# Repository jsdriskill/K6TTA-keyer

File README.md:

# K6TTA Keyer (Raspberry Pi Pico)

CW paddle keyer for RP2040 with SSD1306 UI, rotary encoder setup, flash-backed settings, and a USB composite device: K1EL WinKeyer v2-style serial port, a USB audio source that mirrors the sidetone, and USB MIDI key events.

## Pins

| Function | GPIO |
| --- | --- |
| Dit paddle (active low, external pull-up) | 2 |
| Dash paddle (active low, external pull-up) | 3 |
| TX key out | 4 |
| Sidetone (PWM sine) | 5 |
| Encoder A | 6 |
| Encoder B | 7 |
| Encoder switch | 8 |
| Message button 1 / 2 / 3 (active low, pull-up) | 9 / 10 / 11 |
| OLED SDA (I2C0) | 12 |
| OLED SCL | 13 |
| SSD1306 address | 0x3C |

**Sidetone (pin 5).** A sine wave made with the PWM as a one-pin DAC: 11-bit steps, about 61 kHz carrier and sample rate, a 256-point sine table with linear interpolation, and 4 ms attack/release ramps (no key clicks). The pin swings between 0 V and 3.3 V, so use a series resistor and, for a speaker, a coupling capacitor; a piezo can be driven directly. A small low-pass (for example 1 kohm + 100 nF) removes the 61 kHz carrier if you feed an amplifier. The tone is always at full amplitude, so scale it down with the series resistor or an external volume control. The wave comes from a PWM wrap interrupt on core 0, about 3 % of that core; the pin is parked low whenever the tone is off.

## Build

Uses Pico SDK 2.3.1 from `~/.pico-sdk` when the VS Code Pico extension CMake snippet is present.

```bash
export PICO_SDK_PATH="$HOME/.pico-sdk/sdk/2.3.1"
cmake -S . -B build -DPICO_BOARD=pico
cmake --build build
```

For Pico 2, pass `-DPICO_BOARD=pico2`.

Flash `build/k6tta-keyer.uf2` by holding BOOTSEL, plugging USB, and copying the UF2.

## USB

The keyer enumerates as one composite device ("K6TTA Keyer"):

| Function | What the host sees |
| --- | --- |
| Serial (CDC) | WinKeyer v2-style port |
| Audio | A mono 48 kHz, 16-bit USB microphone ("K6TTA Keyer Sidetone", UAC2). It carries the same sidetone as the buzzer: same frequency, silent when sidetone is disabled in the menu, 4 ms attack/release ramps. Windows needs 10 (1703) or later; macOS and Linux work out of the box. |
| MIDI | A class-compliant MIDI device ("K6TTA Keyer MIDI") |

### MIDI messages

MIDI follows the [Vail adapter MIDI spec](https://github.com/Vail-CW/vail-adapter/blob/master/docs/MIDI_INTEGRATION_SPEC.md), which web CW tools such as Vail and VBand-style adapters use. Channel 1:

| Event | Message |
| --- | --- |
| Key down (each dit/dah element, or straight key down) | Note On, note 0, velocity 127 (`90 00 7F`) |
| Key up | Note Off, note 0 (`80 00 00`) |

The keyer does its own iambic/ultimatic/bug timing, so it reports keyed elements on note 0 (as Vail adapters do in their keyer modes) rather than raw paddle contacts on notes 1 and 2. Incoming MIDI (mode, speed, keyer-type messages) is ignored: configure the keyer from its menu or over WinKeyer.

### Keyer behaviour (K3NG-compatible)

Paddle element generation follows the [K3NG keyer](https://github.com/k3ng/k3ng_cw_keyer): one memory per paddle; while an element and its gap are timed only the *opposite* paddle is sampled, and both paddles are sampled by level when they end. The next element is the remembered opposite one, else a repeat. Iambic A drops the memory when a squeeze is gone by the end of the element. Ultimatic mode uses K3NG's last-touch closure logic. Weighting changes key-down time without changing the spacing (dit + gap = 2 units, dah + gap = 4 units at a 3:1 ratio, as in K3NG), and autospace adds 2 units so the character gap is 3. Differences: paddle contacts are debounced (2 ms), and bug mode only keys down for a dah that is still held. The behaviour is checked against a literal port of K3NG's logic on random paddle input (all four modes) and against its timing formulas.

## WinKeyer serial port

Open the CDC port (`/dev/ttyACM0`, any baud rate), send the host-open command (`00 02`; the reply is the revision byte, 23), then:

- **Text** (ASCII `0x20`-`0x7F`) is sent as Morse through the same timing as the paddles (speed, weighting, dash ratio, sidetone, key output, USB audio and MIDI). It goes through a 128 character buffer. Touching a paddle cancels whatever is queued (break-in).
- **Status byte** (`11` + `BUSY`/`BREAKIN`/`XOFF`) is sent whenever it changes, and on request (`15`). `XOFF` is set when the buffer is more than two thirds full; the `WAIT` and `KEYED` bits are never set.
- **Echo**: characters are echoed as they start sending when the mode register's serial-echo bit (bit 2) is set, and characters sent on the paddles are decoded and echoed when paddle echo (bit 6) is set.
- **Setup commands implemented**: sidetone (`01`, 4000/n Hz), speed (`02`), weighting (`03`), speed pot read (`07`, always minimum), clear buffer (`0A`), mode register (`0E`: keyer mode, paddle swap, autospace, echo bits), status request (`15`), and admin open/close/reset/echo test.
- **Accepted but ignored** (their parameter bytes are consumed so the stream stays in sync): PTT timing, speed pot setup, pause, pin config, key immediate, HSCW, Farnsworth, load defaults, first extension, key compensation, paddle switchpoint, software paddle, buffer pointer, dah ratio, PTT, and the buffered commands (key, wait, merge letters, speed change, HSCW, NOP).
- **Not implemented**: admin calibrate, paddle and speed A2D, get values and EEPROM commands produce no reply.

### Notes

- All USB runs on core 1, so the display and encoder cannot disturb the audio. Core 0 only passes the key state across.
- Saving settings pauses core 1 for a few tens of milliseconds, so the audio may click once when you leave the setup menu.
- The device uses the TinyUSB test vendor id (`0xCafe`). Replace `idVendor`/`idProduct` in `usb_descriptors.c` with your own allocation if you distribute it.
- USB stdio (`printf` over USB) is no longer available; the USB port belongs to the composite device.

## Controls

- Encoder: WPM on the home screen; current menu value in setup
- Click: enter setup, then advance items; last click saves to flash and returns home

## Power-up

The paddle inputs (GPIO 2 and 3) are plain inputs with the internal pull-up and pull-down both off, so each needs an external pull-up resistor to 3.3 V (never 5 V). I use a stiff 680 ohm pull-up, which passes about 5 mA through the key's contacts when they close. That wetting current keeps the contacts clean and reliable, and the low impedance also makes the lines harder for RF to disturb. A weaker pull-up such as 10 kohm also works. Without it the lines float and the keyer sees random paddle contacts. The resistor takes a moment to charge any capacitance on the lines (filter capacitors, a long cable). The keyer waits up to 50 ms at start-up for both lines to go high, and then ignores the paddles until it has seen both released, so contacts that are closed or still settling at power-up never send anything.

## Setup menu

Click the encoder to open the menu and again to step to the next page. Each page shows what is being changed on the top line (large type, centred), its value on the line below (large type, inverted), and the page number (for example 3/9) at the bottom. Turn the encoder to change the value.

## Main screen

The speed (large digits) and the mode are shown at boot. As soon as anything is sent, the screen switches to the text that has been sent, in large type: four lines of 11 characters, word wrapped, scrolling up one line at a time when the bottom line is full. It shows what the paddles sent (decoded with the same Morse table the WinKeyer sender uses; the prosigns BT, AR and SK are shown as `<BT>`, `<AR>` and `<SK>`, and a pattern that is not a character shows `*`), plus stored messages and text sent from the WinKeyer port. The text stays until reboot. Turning the encoder, or a speed change from the WinKeyer host, shows the speed for 3 seconds (each change restarts the timer), then the text returns. In bug and straight-key modes nothing is decoded and the speed screen stays. The TEXT setting in the setup menu (last page) turns the text display off, which leaves the speed screen on all the time.

## Stored messages

Three messages of up to 32 characters each, on the buttons at GPIO 9, 10 and 11 (to ground).

- Short press: send the message at the current speed. Press again while it is sending to abort. Touching a paddle also aborts. A slot with no message goes straight to edit mode.
- Hold 3 seconds: edit that slot. Button presses are ignored while the setup menu is open.
- Editing starts with the cursor just after the stored message (on "done"). The whole message is shown in large type, four lines of 11 characters, with the cursor inverted. The encoder chooses the character at the cursor (done, space, A-Z, 0-9, `. , ? /`), and the encoder button stores it and moves on. Button 1 / button 2 move the cursor back / forward without changing anything (an unstored change is dropped). Choosing "done" and clicking saves the message up to the cursor; "done" at the first position leaves the slot empty. Filling all 32 positions saves and exits automatically.
- The messages live in the settings flash page; saving takes about 50 ms, during which USB audio drops out.

## Hardware

KiCad projects for the main and front boards are in [`hardware/`](hardware/README.md) (draft v0.1: parts placed, not yet routed).

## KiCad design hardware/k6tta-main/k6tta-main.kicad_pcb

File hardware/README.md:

# K6TTA keyer hardware v0.1

Two KiCad 10 projects. Both boards are routed with GND pours on both layers and pass DRC
(only cosmetic silkscreen and library-version warnings remain).

* `k6tta-main/` main board, 64 x 56 mm: RP2040-Zero on sockets (USB-C to the rear), rig jack at the rear facing back,
  paddle jack front-right, headphone jack left with the thumbwheel in front of it, 2x8 right-angle socket on the front edge.
* `k6tta-front/` front board, 76 x 54 mm: 0.96in SSD1306 OLED (on a 1x4 socket), EC11 encoder, three 12 mm message buttons,
  2x8 straight header soldered on the BACK so it plugs into the main board's right-angle socket.

Pin assignments come from `config.h` (GP2 dit, GP3 dah, GP4 TX key, GP5 sidetone, GP6-8 encoder,
GP9-11 message buttons, GP12/13 I2C).

The KiCad files are the source of truth. The scripts in `generator/` produced the first unrouted draft and the
netlist/BOM CSVs; part positions in them no longer match the routed boards.

## Checked

* **RP2040-Zero pinout** (`K6TTA:RP2040-Zero_Socketed`): pad 1 = 5V top-left with USB-C up, GP0 top-right,
  GP9..GP13 on the short row opposite the USB (GP13 at the left). Confirmed against the clone in use.
* **Thumbwheel RV1** (Alps RK10J11E0034, `K6TTA:Alps_RK10J_Thumbwheel_5pin`): footprint checked against the Alps
  PC board drawing. It is a single pot: pads 1, 3, 5 = datasheet pins 1 (end), 2 (wiper), 3 (end); pads 2 and 4
  are dummy terminals. Wired as a rheostat: VOL_IN to pad 1, wiper (pad 3) tied to pad 5 and the headphones.

## Still to check

* **Board-to-board header**: main J5 odd pins (rear row of the right-angle socket, upper opening) carry the signals;
  front J1 even pins (upper row) mate with them. Check the height of the socket openings against where the front board sits.
* **OLED module**: pin order GND VCC SCL SDA; it is held only by its socket, so support it with standoffs or the panel.
* **LCSC numbers**: all JLCPCB-placed parts are chosen from the Basic library (the "JLC class" column says which were
  confirmed); re-check stock when you order.

R8 (speaker series resistor) is a 1/2 W axial part you solder, so you can change the speaker level.

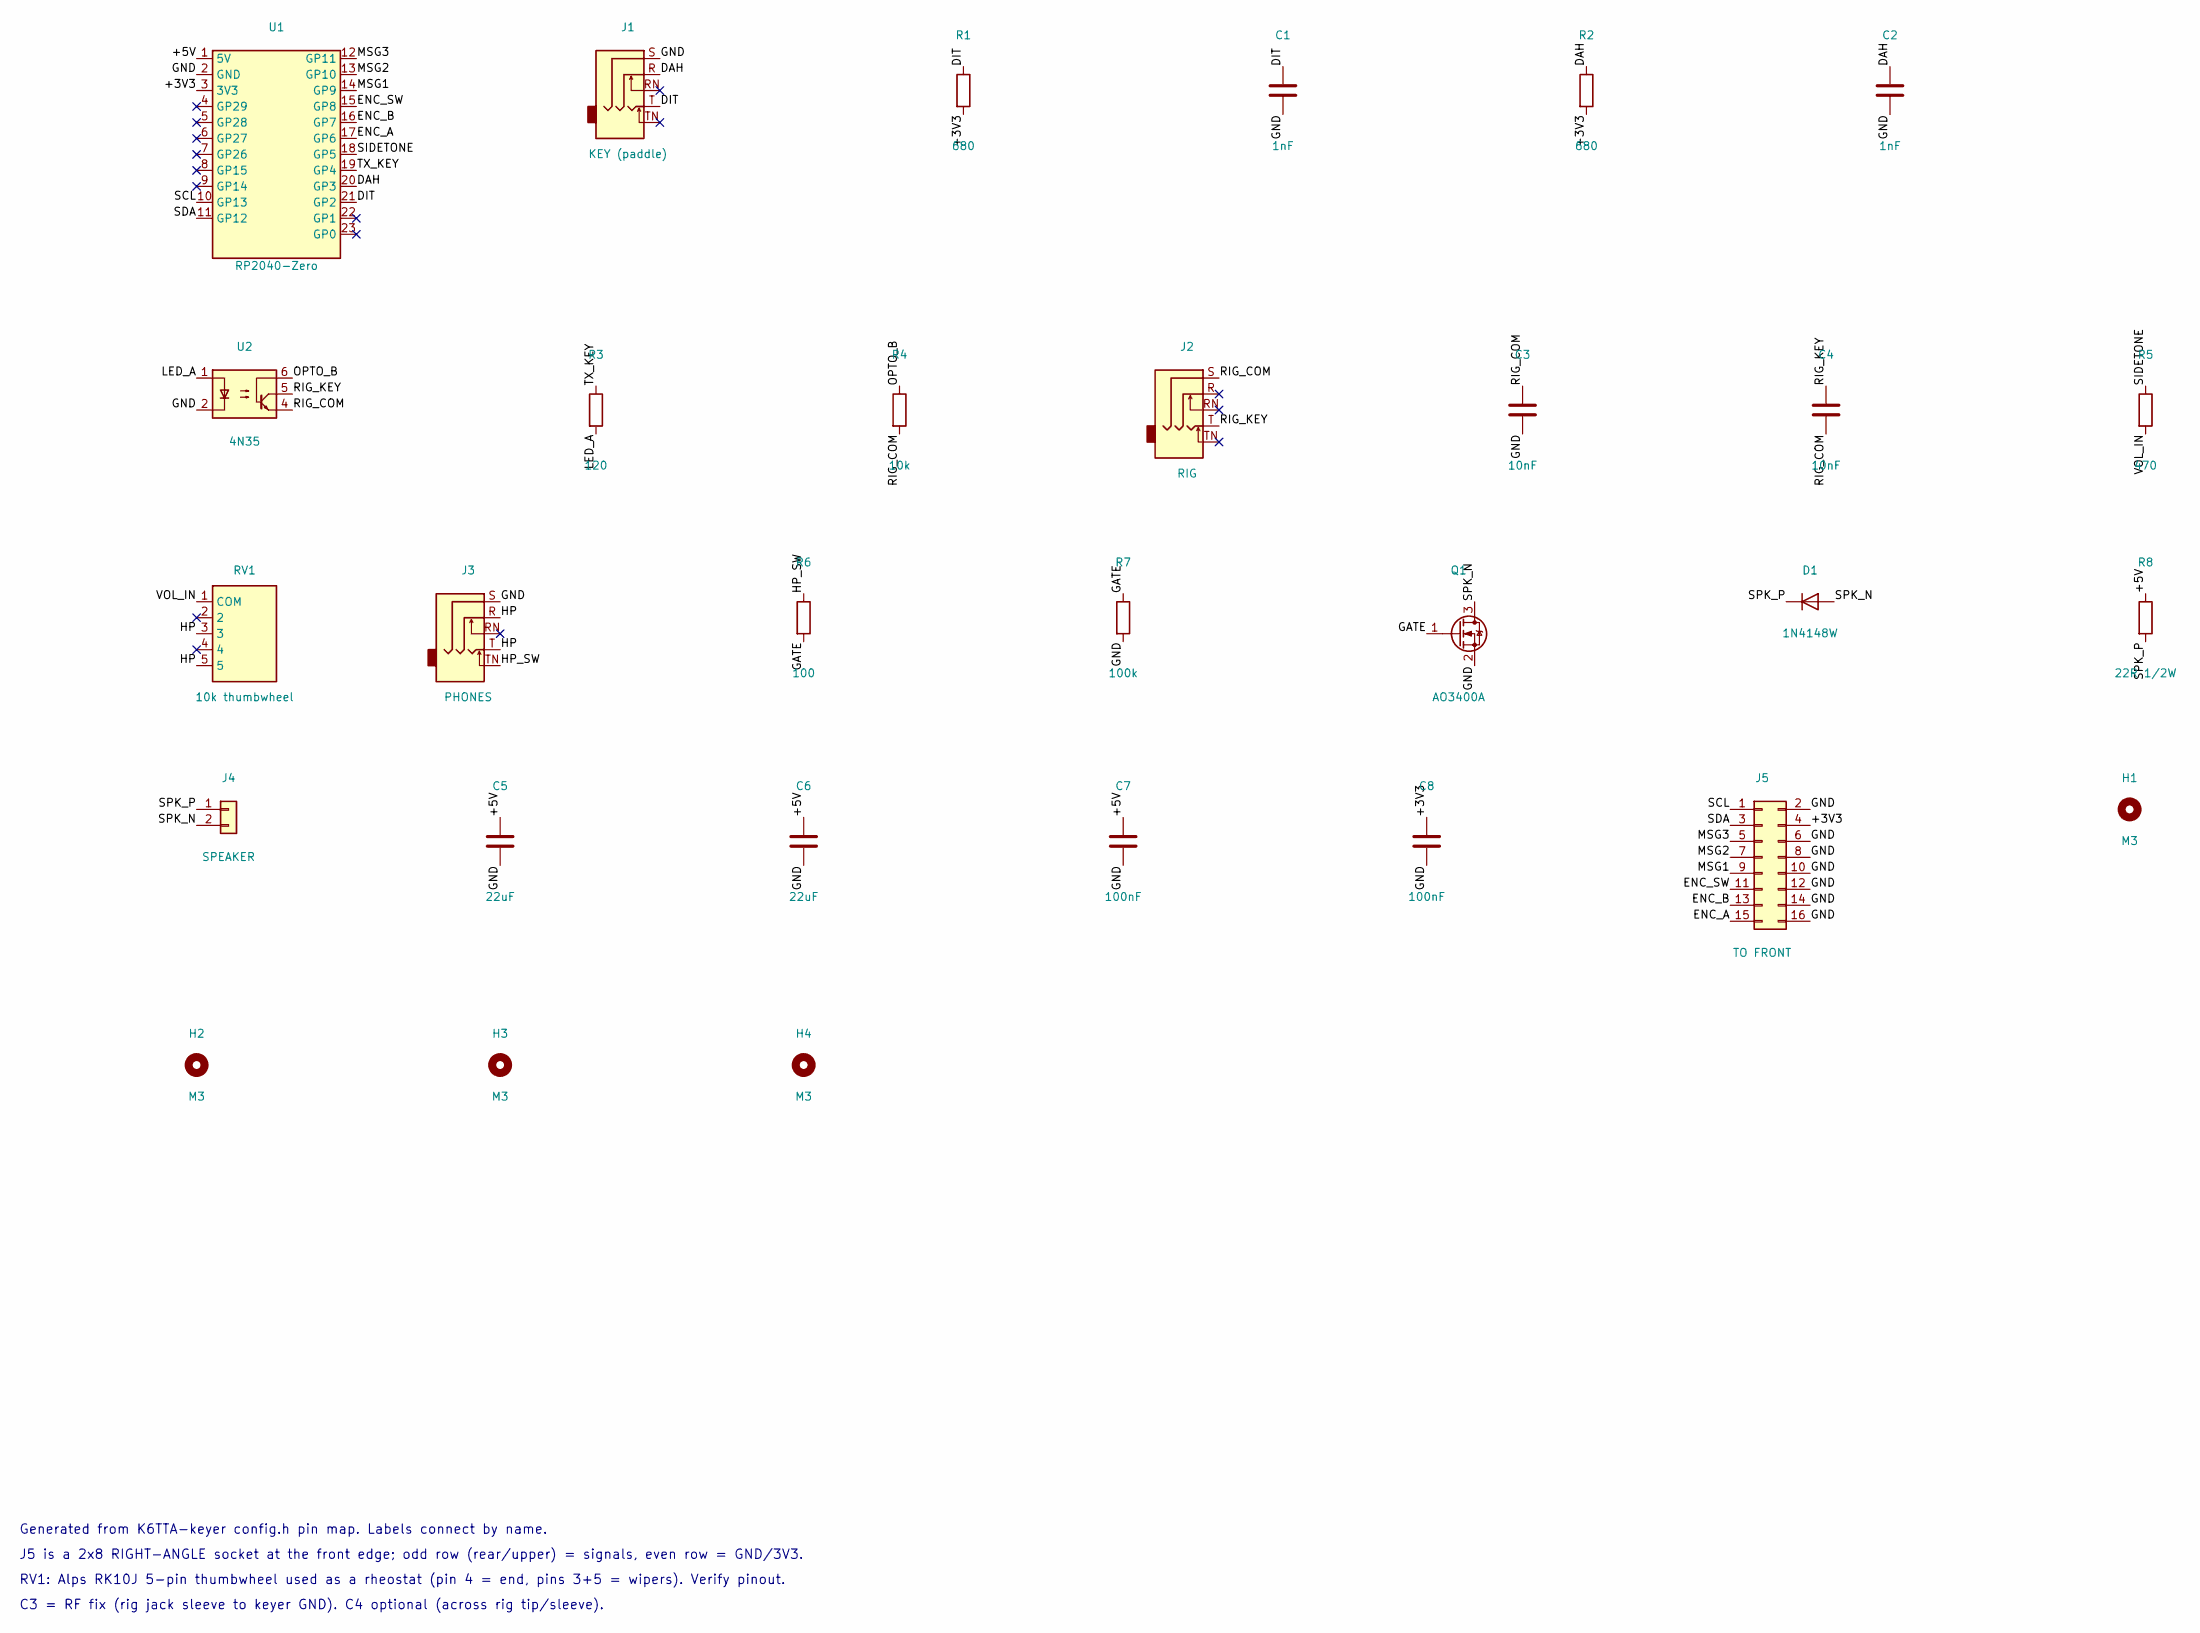
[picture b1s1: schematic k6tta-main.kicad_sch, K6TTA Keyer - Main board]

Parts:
C1, C2: 1nF; C_0805_2012Metric; LCSC C46653
C3, C4: 10nF; C_0805_2012Metric; LCSC C1710
C5, C6: 22uF; C_0805_2012Metric; LCSC C45783
C7, C8: 100nF; C_0805_2012Metric; LCSC C49678
D1: 1N4148W; D_SOD-123; LCSC C81598
H1, H2, H3, H4: M3; MountingHole_3.2mm_M3
J1: KEY (paddle); Jack_3.5mm_CUI_SJ1-3525N_Horizontal; MPN/Notes Same Sky SJ1-3525N
J2: RIG; Jack_3.5mm_CUI_SJ1-3525N_Horizontal; MPN/Notes Same Sky SJ1-3525N
J3: PHONES; Jack_3.5mm_CUI_SJ1-3525N_Horizontal; MPN/Notes Same Sky SJ1-3525N
J4: SPEAKER; JST_XH_B2B-XH-A_1x02_P2.50mm_Vertical; MPN/Notes JST B2B-XH-A
J5: TO FRONT; PinSocket_2x08_P2.54mm_Horizontal; MPN/Notes 2x8 female socket, right angle, 2.54mm
Q1: AO3400A; SOT-23; LCSC C20917
R1, R2: 680; R_0805_2012Metric; LCSC C17798
R3: 120; R_0805_2012Metric; LCSC C17437
R4: 10k; R_0805_2012Metric; LCSC C17414
R5: 470; R_0805_2012Metric; LCSC C17710
R6: 100; R_0805_2012Metric; LCSC C17408
R7: 100k; R_0805_2012Metric; LCSC C149504
R8: 22R 1/2W; R_Axial_DIN0207_L6.3mm_D2.5mm_P7.62mm_Horizontal; MPN/Notes 22 ohm 0.5W axial (change value to set 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
RV1: 10k thumbwheel; Alps_RK10J_Thumbwheel_5pin; MPN/Notes Alps RK10J11E0034; LCSC C470643
U1: RP2040-Zero; RP2040-Zero_Socketed
U2: 4N35; DIP-6_W7.62mm; MPN/Notes 4N35 DIP-6 (socket optional)

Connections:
/+3V3: C8.1, J5.4, R1.2, R2.2, U1.3 (3V3)
/+5V: C5.1, C6.1, C7.1, R8.1, U1.1 (5V)
/DAH: C2.1, J1.R, R2.1, U1.20 (GP3)
/DIT: C1.1, J1.T, R1.1, U1.21 (GP2)
/ENC_A: J5.15, U1.17 (GP6)
/ENC_B: J5.13, U1.16 (GP7)
/ENC_SW: J5.11, U1.15 (GP8)
/GATE: Q1.1 (G), R6.2, R7.1
/GND: C1.2, C2.2, C3.2, C5.2, C6.2, C7.2, C8.2, J1.S, J3.S, J5.2, J5.6, J5.8, J5.10, J5.12, J5.14, J5.16, Q1.2 (S), R7.2, U1.2 (GND), U2.2
/HP: J3.R, J3.T, RV1.3, RV1.5
/HP_SW: J3.TN, R6.1
/LED_A: R3.2, U2.1
/MSG1: J5.9, U1.14 (GP9)
/MSG2: J5.7, U1.13 (GP10)
/MSG3: J5.5, U1.12 (GP11)
/OPTO_B: R4.1, U2.6
/RIG_COM: C3.1, C4.2, J2.S, R4.2, U2.4
/RIG_KEY: C4.1, J2.T, U2.5
/SCL: J5.1, U1.10 (GP13)
/SDA: J5.3, U1.11 (GP12)
/SIDETONE: R5.1, U1.18 (GP5)
/SPK_N: D1.2 (A), J4.2, Q1.3 (D)
/SPK_P: D1.1 (K), J4.1, R8.2
/TX_KEY: R3.1, U1.19 (GP4)
/VOL_IN: R5.2, RV1.1 (COM)

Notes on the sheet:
J5 is a 2x8 RIGHT-ANGLE socket at the front edge; odd row (rear/upper) = signals, even row = GND/3V3.
RV1: Alps RK10J 5-pin thumbwheel used as a rheostat (pin 4 = end, pins 3+5 = wipers). Verify pinout.
Generated from K6TTA-keyer config.h pin map. Labels connect by name.
C3 = RF fix (rig jack sleeve to keyer GND). C4 optional (across rig tip/sleeve).

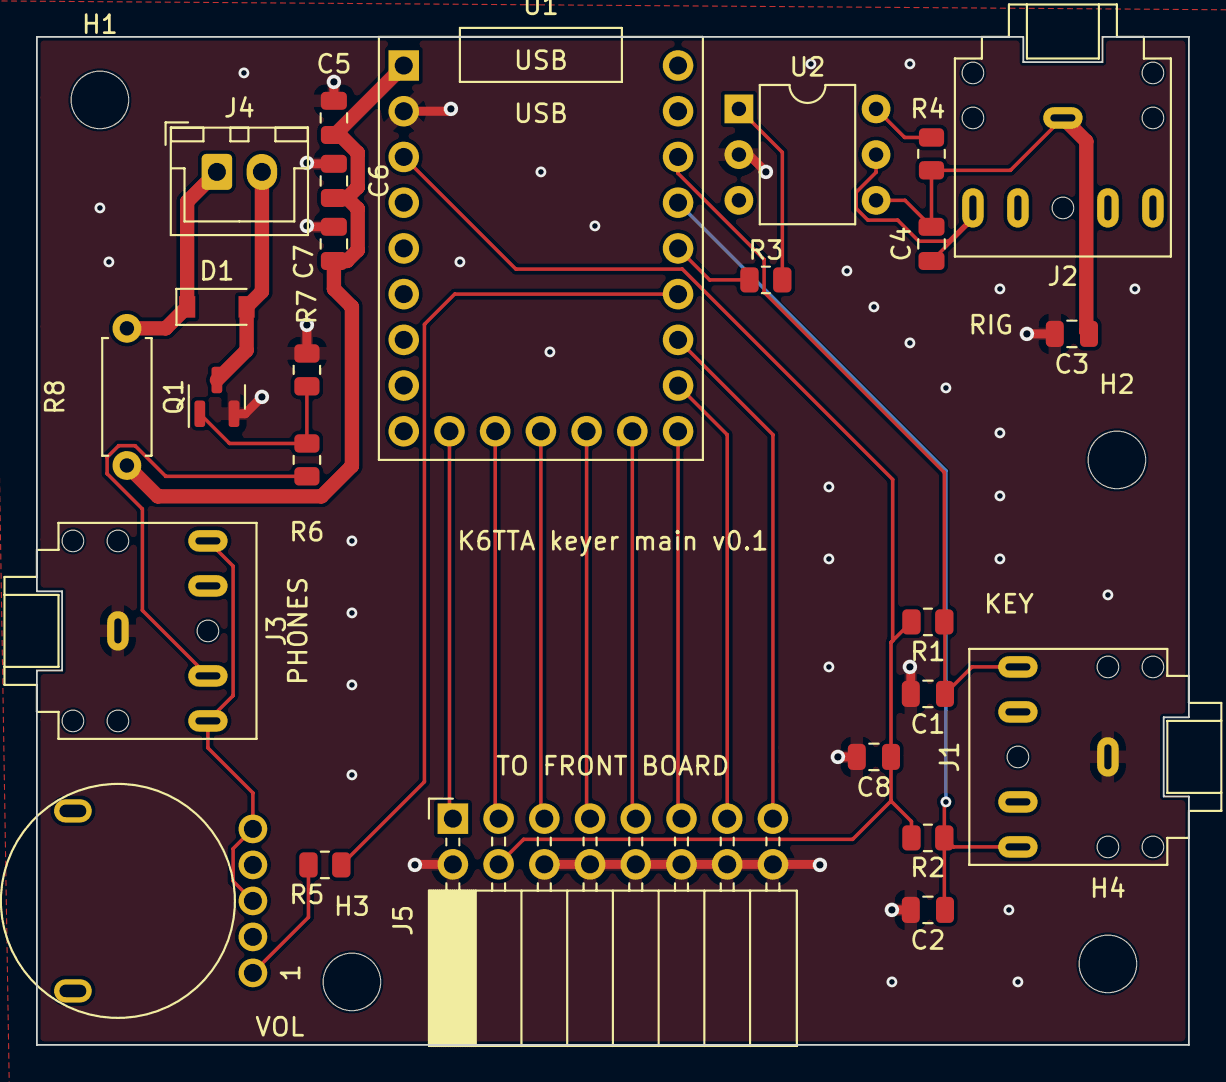
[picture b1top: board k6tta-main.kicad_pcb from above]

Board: 2 copper layers, 64.0 x 56.0 mm, 30 parts (0 on the bottom side), 25 nets.

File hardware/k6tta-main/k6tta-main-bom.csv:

Qty,Designators,Value,Footprint,LCSC,JLC class,Part / notes,Who solders
2,C1 C2,1nF,C_0805_2012Metric,C46653,0805 50V basic (confirmed),,JLCPCB
2,C3 C4,10nF,C_0805_2012Metric,C1710,0805 50V basic (confirmed),,JLCPCB
2,C5 C6,22uF,C_0805_2012Metric,C45783,0805 25V X5R basic (confirmed),,JLCPCB
2,C7 C8,100nF,C_0805_2012Metric,C49678,0805 50V basic,,JLCPCB
1,D1,1N4148W,D_SOD-123,C81598,SOD-123 basic,,JLCPCB
1,J1,KEY (paddle),Jack_3.5mm_CUI_SJ1-3525N_Horizontal,,,Same Sky SJ1-3525N,you
1,J2,RIG,Jack_3.5mm_CUI_SJ1-3525N_Horizontal,,,Same Sky SJ1-3525N,you
1,J3,PHONES,Jack_3.5mm_CUI_SJ1-3525N_Horizontal,,,Same Sky SJ1-3525N,you
1,J4,SPEAKER,JST_XH_B2B-XH-A_1x02_P2.50mm_Vertical,,,JST B2B-XH-A,you
1,J5,TO FRONT,PinSocket_2x08_P2.54mm_Horizontal,,,"2x8 female socket, right angle, 2.54mm",you
1,Q1,AO3400A,SOT-23,C20917,basic (confirmed),,JLCPCB
2,R1 R2,680,R_0805_2012Metric,C17798,0805 basic (confirmed),,JLCPCB
1,R3,120,R_0805_2012Metric,C17437,0805 basic (confirmed),,JLCPCB
1,R4,10k,R_0805_2012Metric,C17414,0805 basic,,JLCPCB
1,R5,470,R_0805_2012Metric,C17710,0805 basic,,JLCPCB
1,R6,100,R_0805_2012Metric,C17408,0805 basic,,JLCPCB
1,R7,100k,R_0805_2012Metric,C149504,0805 basic,,JLCPCB
1,R8,22R 1/2W,R_Axial_DIN0207_L6.3mm_D2.5mm_P7.62mm_Horizontal,,,22 ohm 0.5W axial (change value to set speaker level),you
1,RV1,10k thumbwheel,Alps_RK10J_Thumbwheel_5pin,C470643,,"Alps RK10J11E0034; Rheostat: pin4 = end, pins 3+5 = wipers under both published pinouts. VERIFY footprint.",you
1,U1,RP2040-Zero,RP2040-Zero_Socketed,,,"Waveshare RP2040-Zero (clone) on 2.54mm female headers 1x9, 1x9, 1x5; USB-C to rear",you
1,U2,4N35,DIP-6_W7.62mm,,,4N35 DIP-6 (socket optional),you

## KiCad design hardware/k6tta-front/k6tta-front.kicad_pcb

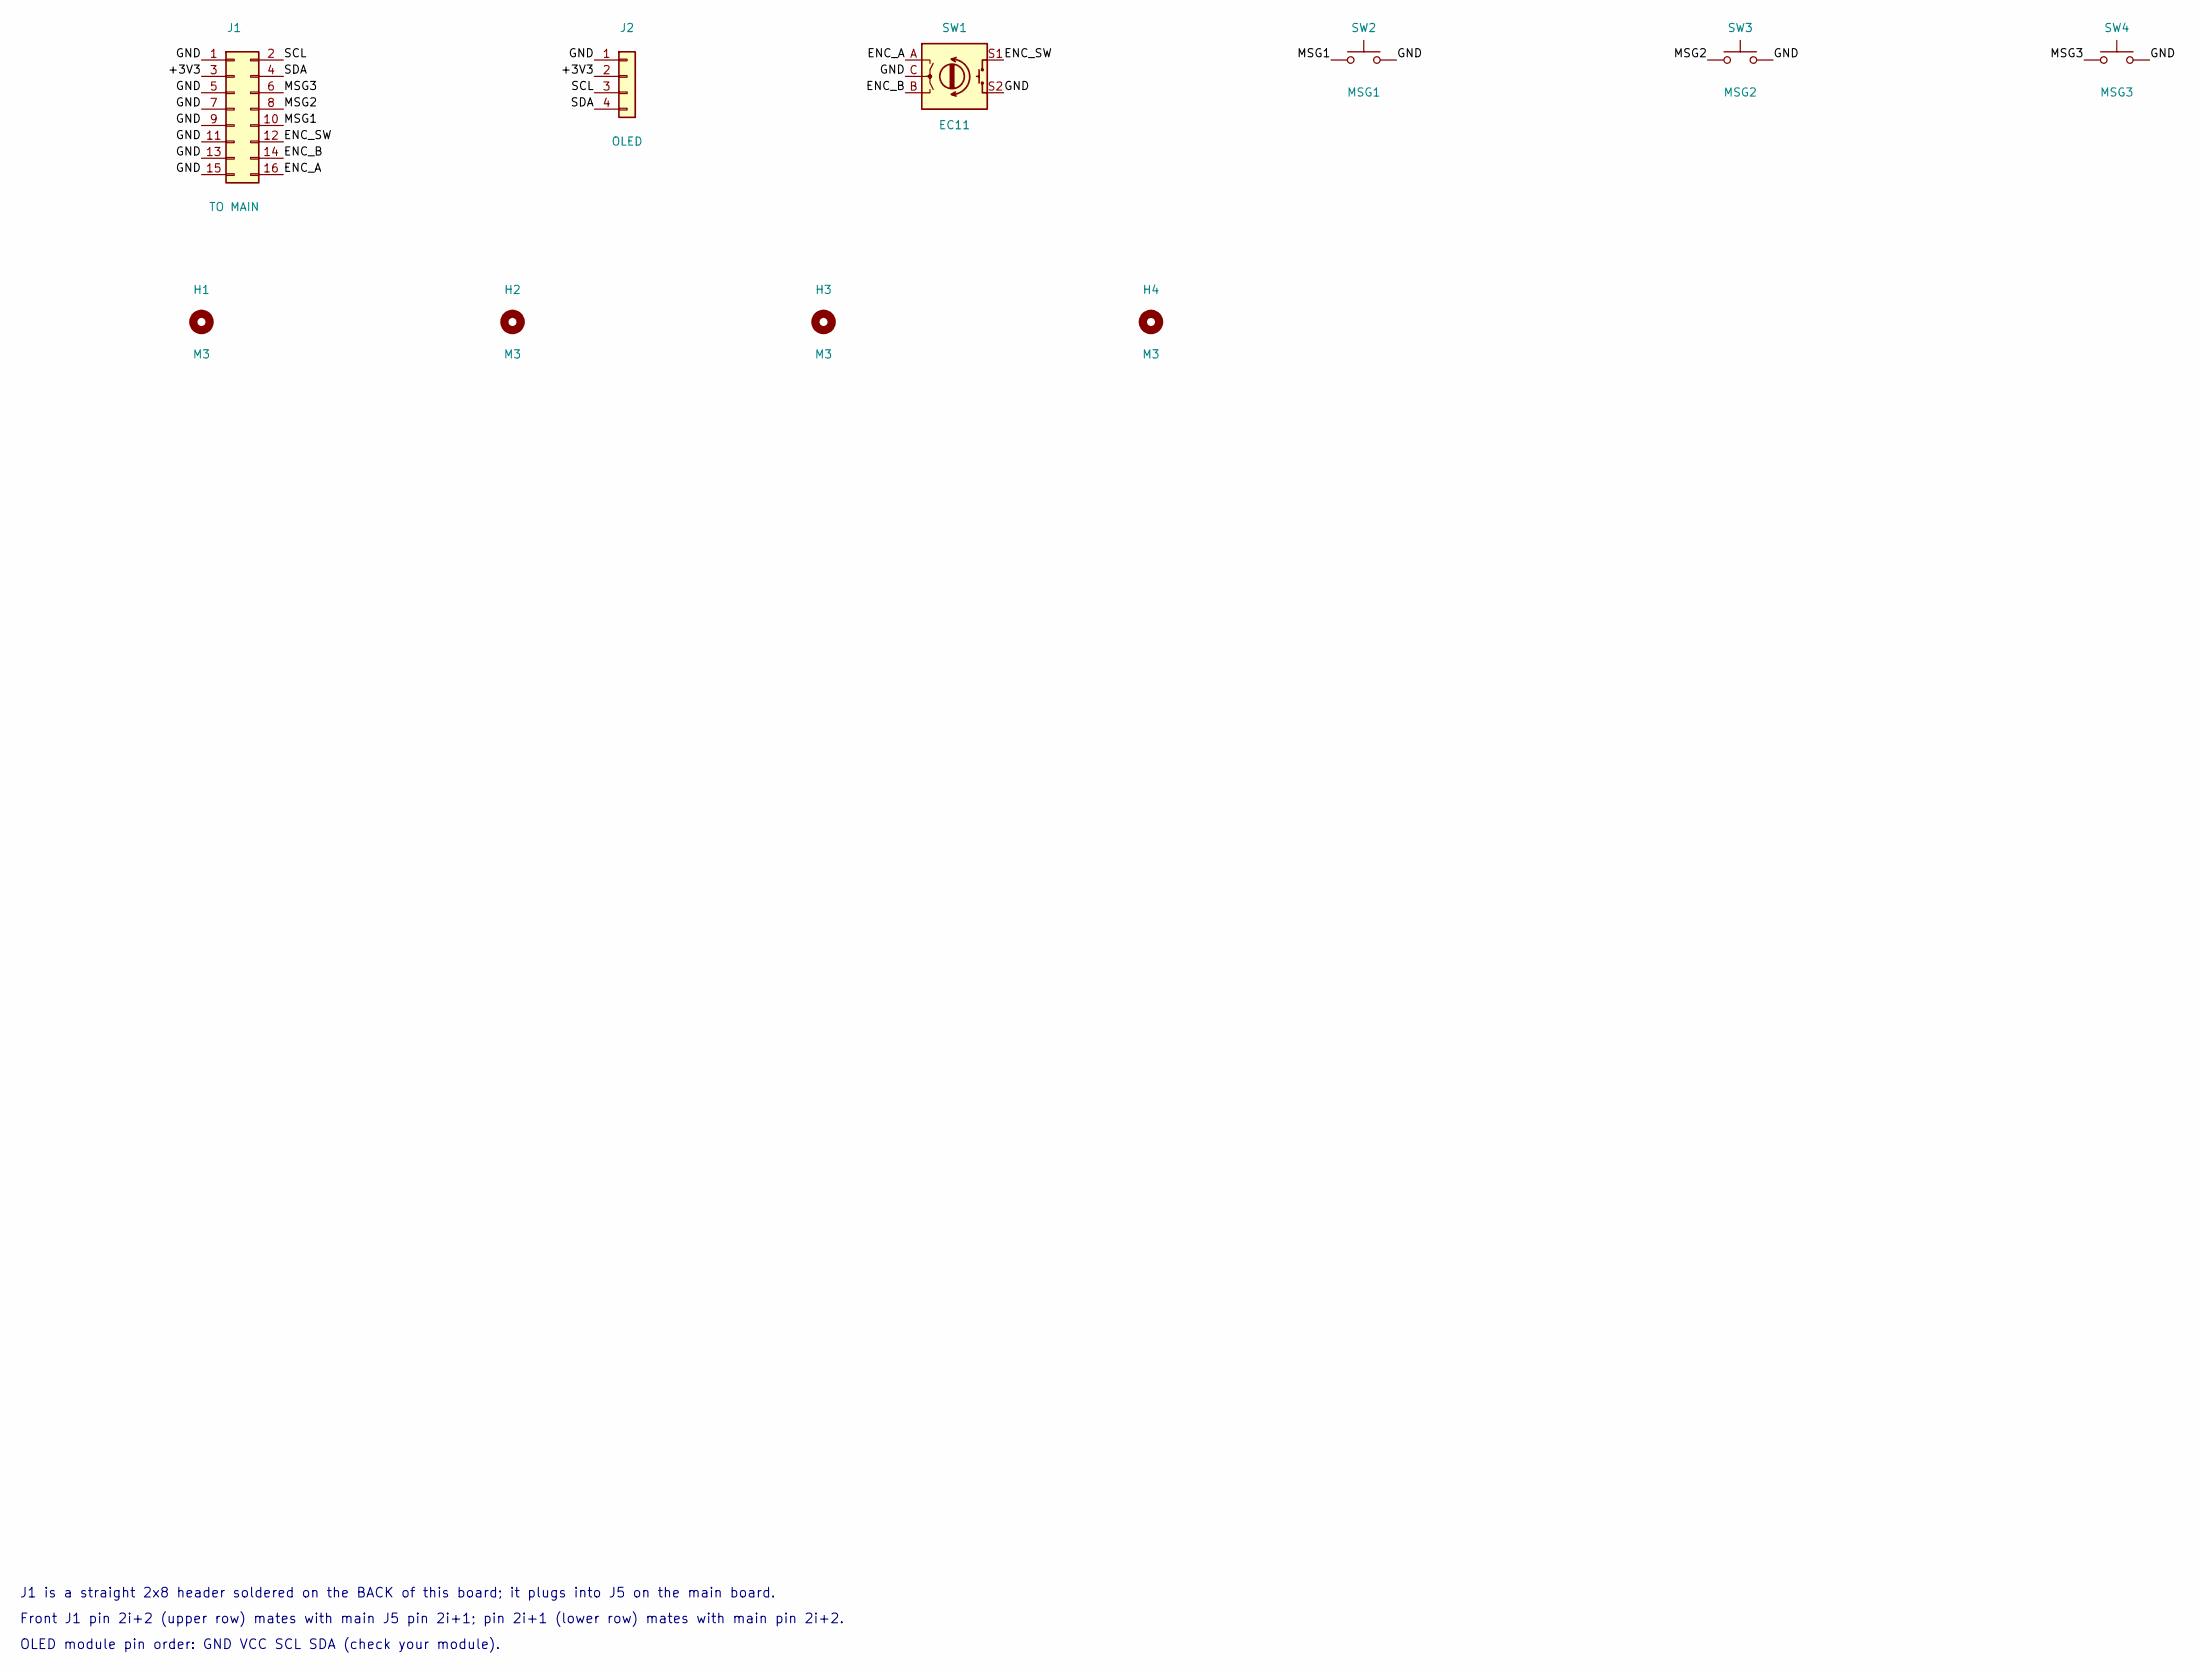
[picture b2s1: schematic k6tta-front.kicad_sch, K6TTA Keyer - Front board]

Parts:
H1, H2, H3, H4: M3; MountingHole_3.2mm_M3
J1: TO MAIN; PinHeader_2x08_P2.54mm_Vertical; MPN/Notes 2x8 male header 2.54mm, straight; MOUNT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
J2: OLED; PinSocket_1x04_P2.54mm_Vertical; MPN/Notes 1x4 female header for 0.96in SSD1306 I2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
SW1: EC11; RotaryEncoder_Alps_EC11E-Switch_Vertical_H20mm; MPN/Notes EC11 with push switch
SW2: MSG1; SW_PUSH-12mm; MPN/Notes Omron B3F-4055 + B32-2000 series cap; LCSC C84931
SW3: MSG2; SW_PUSH-12mm; MPN/Notes Omron B3F-4055 + B32-2000 series cap; LCSC C84931
SW4: MSG3; SW_PUSH-12mm; MPN/Notes Omron B3F-4055 + B32-2000 series cap; LCSC C84931

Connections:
/+3V3: J1.3, J2.2
/ENC_A: J1.16, SW1.A
/ENC_B: J1.14, SW1.B
/ENC_SW: J1.12, SW1.S1
/GND: J1.1, J1.5, J1.7, J1.9, J1.11, J1.13, J1.15, J2.1, SW1.C, SW1.S2, SW2.2, SW3.2, SW4.2
/MSG1: J1.10, SW2.1
/MSG2: J1.8, SW3.1
/MSG3: J1.6, SW4.1
/SCL: J1.2, J2.3
/SDA: J1.4, J2.4

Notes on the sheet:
OLED module pin order: GND VCC SCL SDA (check your module).
Front J1 pin 2i+2 (upper row) mates with main J5 pin 2i+1; pin 2i+1 (lower row) mates with main pin 2i+2.
J1 is a straight 2x8 header soldered on the BACK of this board; it plugs into J5 on the main board.

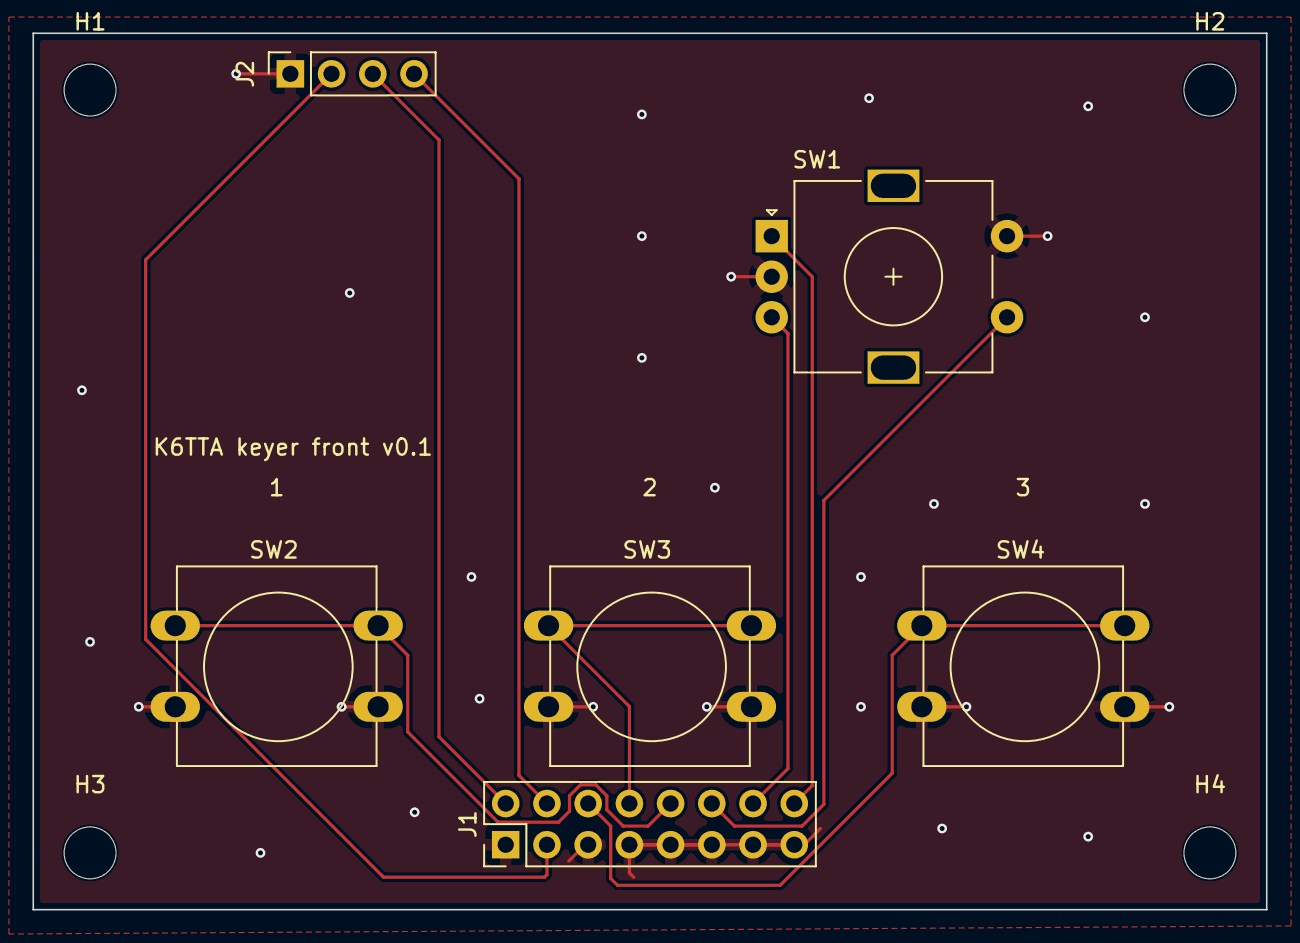
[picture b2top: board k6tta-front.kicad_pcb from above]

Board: 2 copper layers, 76.0 x 54.0 mm, 10 parts (0 on the bottom side), 10 nets.

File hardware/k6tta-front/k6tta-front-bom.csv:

Qty,Designators,Value,Footprint,LCSC,JLC class,Part / notes,Who solders
1,J1,TO MAIN,PinHeader_2x08_P2.54mm_Vertical,,,"2x8 male header 2.54mm, straight; MOUNT ON BACK",you
1,J2,OLED,PinSocket_1x04_P2.54mm_Vertical,,,1x4 female header for 0.96in SSD1306 I2C module (GND VCC SCL SDA),you
1,SW1,EC11,RotaryEncoder_Alps_EC11E-Switch_Vertical_H20mm,,,EC11 with push switch,you
1,SW2,MSG1,SW_PUSH-12mm,C84931,,Omron B3F-4055 + B32-2000 series cap,you
1,SW3,MSG2,SW_PUSH-12mm,C84931,,Omron B3F-4055 + B32-2000 series cap,you
1,SW4,MSG3,SW_PUSH-12mm,C84931,,Omron B3F-4055 + B32-2000 series cap,you

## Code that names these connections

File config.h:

#ifndef CONFIG_H
#define CONFIG_H

#include <stdint.h>
#include <stdbool.h>
#include "hardware/i2c.h"

#define PIN_PADDLE_DIT     2
#define PIN_PADDLE_DASH    3
#define PIN_TX_KEY         4
#define PIN_SIDETONE_PWM   5

/* Stored-message buttons: active low, internal pull-ups */
#define PIN_MSG1           9
#define PIN_MSG2           10
#define PIN_MSG3           11

#define PIN_ENC_A          6
#define PIN_ENC_B          7
#define PIN_ENC_SW         8

/* Quadrature transitions per physical detent (click). Most mechanical
 * encoders (e.g. EC11 with 20 detents) give 4; some give 2 (rests at both
 * 00 and 11) or 1. If one click moves the value by N, set this to N. */
#ifndef ENC_STEPS_PER_DETENT
#define ENC_STEPS_PER_DETENT 4
#endif

#define I2C_PORT           i2c0
#define PIN_I2C_SDA        12
#define PIN_I2C_SCL        13
#define SSD1306_ADDR       0x3C

#define MSG_SLOTS    3
#define MSG_MAX_LEN  32

typedef enum {
    KEYER_MODE_IAMBIC_B = 0,
    KEYER_MODE_IAMBIC_A,
    KEYER_MODE_ULTIMATE,
    KEYER_MODE_BUG,
    KEYER_MODE_STRAIGHT
} KeyerMode;

typedef struct __attribute__((packed)) {
    uint8_t  magic;
    uint8_t  wpm;
    uint8_t  sidetone_en;
    uint16_t sidetone_freq;
    uint8_t  weighting;
    uint8_t  dash_ratio;
    uint8_t  mode;
    uint8_t  paddle_swap;
    uint8_t  autospace;
    uint8_t  first_extension;
    uint8_t  show_text;         /* 1 = decoded text on the main screen, 0 = speed only. This byte held the
                                   sidetone volume (1..10) in older saves, so anything but 0 reads as on. */
    char     messages[MSG_SLOTS][MSG_MAX_LEN];   /* stored messages: NUL-terminated unless full; empty = first byte 0 */
} ConfigSettings;

extern ConfigSettings sys_config;

#endif

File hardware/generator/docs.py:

"""Write netlist checklists, BOMs and a README next to the generated projects."""
import csv, os, sys
import gen

OUT = sys.argv[1]

for board, cfg in gen.BOARDS.items():
    d = os.path.join(OUT, board)
    nets = {}
    for p in cfg["parts"]:
        for pin, net in p["pins"].items():
            if net:
                nets.setdefault(net, []).append("%s.%s" % (p["ref"], pin))
    with open(os.path.join(d, board + "-netlist.csv"), "w", newline="") as f:
        w = csv.writer(f)
        w.writerow(["Net", "Pins"])
        for n in sorted(nets):
            w.writerow([n, " ".join(sorted(nets[n], key=lambda s: (s.split(".")[0], s.split(".")[1].zfill(3))))])
    # full BOM grouped by value+footprint+assembly
    groups = {}
    for p in cfg["parts"]:
        if p["assembly"] == "none":
            continue
        k = (p["value"], p["fp"], p["lcsc"], p["mfr"], p["assembly"], p["note"])
        groups.setdefault(k, []).append(p["ref"])
    with open(os.path.join(d, board + "-bom.csv"), "w", newline="") as f:
        w = csv.writer(f)
        w.writerow(["Qty", "Designators", "Value", "Footprint", "LCSC", "JLC class", "Part / notes", "Who solders"])
        cls = {v[0]: v[1] for v in gen.LC.values()}
        for k, refs in sorted(groups.items(), key=lambda kv: kv[1][0]):
            val, fp, lc, mfr, asm, note = k
            w.writerow([len(refs), " ".join(refs), val, fp.split(":")[1], lc, cls.get(lc, ""), "; ".join(x for x in (mfr, note) if x),
                        "JLCPCB" if asm == "JLC" else "you"])
    jlc = [(k, refs) for k, refs in groups.items() if k[4] == "JLC"]
    if jlc:
        with open(os.path.join(d, board + "-jlcpcb-bom.csv"), "w", newline="") as f:
            w = csv.writer(f)
            w.writerow(["Comment", "Designator", "Footprint", "LCSC Part #"])
            for k, refs in sorted(jlc, key=lambda kv: kv[1][0]):
                w.writerow([k[0], ",".join(refs), k[1].split(":")[1], k[2]])

open(os.path.join(OUT, "README.md"), "w").write("""# K6TTA keyer hardware v0.1

Two KiCad 10 projects. Both boards are routed with GND pours on both layers and pass DRC
(only cosmetic silkscreen and library-version warnings remain).

* `k6tta-main/` main board, 64 x 56 mm: RP2040-Zero on sockets (USB-C to the rear), rig jack at the rear facing back,
  paddle jack front-right, headphone jack left with the thumbwheel in front of it, 2x8 right-angle socket on the front edge.
* `k6tta-front/` front board, 76 x 54 mm: 0.96in SSD1306 OLED (on a 1x4 socket), EC11 encoder, three 12 mm message buttons,
  2x8 straight header soldered on the BACK so it plugs into the main board's right-angle socket.

Pin assignments come from `config.h` (GP2 dit, GP3 dah, GP4 TX key, GP5 sidetone, GP6-8 encoder,
GP9-11 message buttons, GP12/13 I2C).

The KiCad files are the source of truth. The scripts in `generator/` produced the first unrouted draft and the
netlist/BOM CSVs; part positions in them no longer match the routed boards.

## Checked

* **RP2040-Zero pinout** (`K6TTA:RP2040-Zero_Socketed`): pad 1 = 5V top-left with USB-C up, GP0 top-right,
  GP9..GP13 on the short row opposite the USB (GP13 at the left). Confirmed against the clone in use.
* **Thumbwheel RV1** (Alps RK10J11E0034, `K6TTA:Alps_RK10J_Thumbwheel_5pin`): footprint checked against the Alps
  PC board drawing. It is a single pot: pads 1, 3, 5 = datasheet pins 1 (end), 2 (wiper), 3 (end); pads 2 and 4
  are dummy terminals. Wired as a rheostat: VOL_IN to pad 1, wiper (pad 3) tied to pad 5 and the headphones.

## Still to check

* **Board-to-board header**: main J5 odd pins (rear row of the right-angle socket, upper opening) carry the signals;
  front J1 even pins (upper row) mate with them. Check the height of the socket openings against where the front board sits.
* **OLED module**: pin order GND VCC SCL SDA; it is held only by its socket, so support it with standoffs or the panel.
* **LCSC numbers**: all JLCPCB-placed parts are chosen from the Basic library (the "JLC class" column says which were
  confirmed); re-check stock when you order.

R8 (speaker series resistor) is a 1/2 W axial part you solder, so you can change the speaker level.
""")

print("docs written")
